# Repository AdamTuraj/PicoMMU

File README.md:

# PicoMMU

PicoMMU is a PCB designed to control a stepper motor and servo for a multi-material unit. It is compatible with Klipper firmware.

## Requirements

- A USB C cable to connect to your RPI / Printer
- A 12-24V power supply
- A TMC2209 (BTT Recommended)
- A stepper motor crimped with a 4 pin JST XH B4

## Flashing Klipper

1. Follow [this Klipper guide](https://www.klipper3d.org/Installation.html) on how to build the firmware. The first image shows the configuration settings and the second shows the "Optional Features" section.

2. Once the firmware is build, put the chip into DFU mode by clicking the reset button while holding the boot button.
3. Run lsusb and take not of the numbers in this format: xxxx:xxxx.
4. Now use the following command to flash the firmware (replacing xxxx:xxxx with your MCU's ID): `make flash FLASH_DEVICE=xxxx:xxxx`.
5. Unplug and replug in the USB cord and your MCU should pop up in `ls /dev/serial/by-id/*`.

## License

This project is licensed under the MIT License.

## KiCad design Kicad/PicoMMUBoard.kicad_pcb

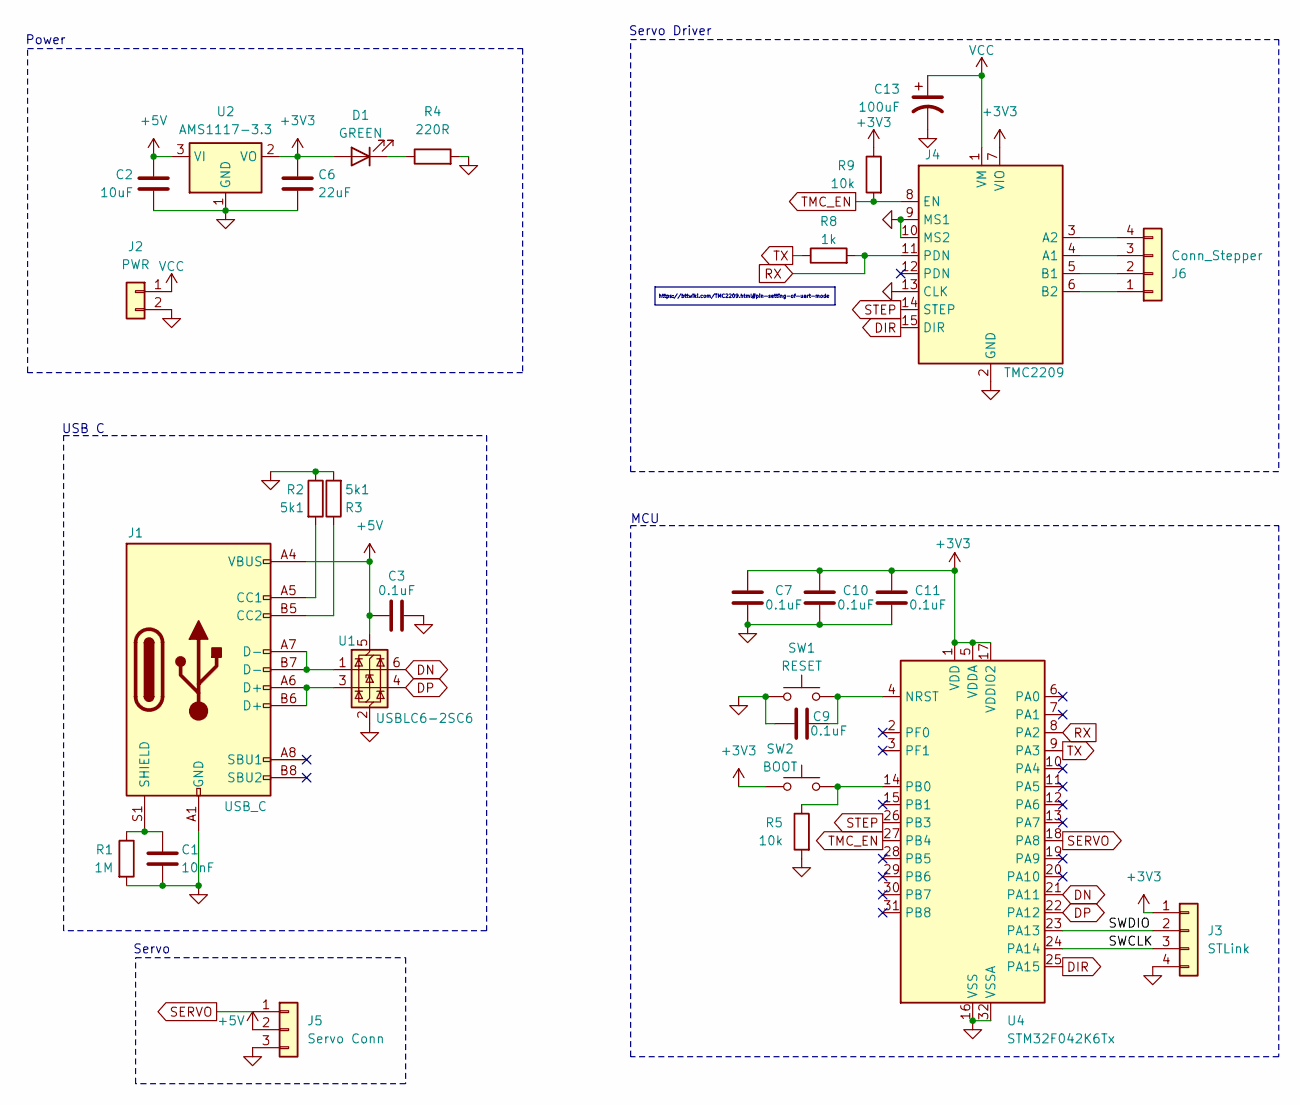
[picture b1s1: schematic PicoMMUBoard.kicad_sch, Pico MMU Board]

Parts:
C1: 10nF; C_0603_1608Metric
C2: 10uF; C_0603_1608Metric
C3, C7, C9, C10, C11: 0.1uF; C_0603_1608Metric
C6: 22uF; C_0603_1608Metric
C13: 100uF; C_Elec_6.3x7.7; LCSC C3151829
D1: GREEN; LED_0805_2012Metric; LCSC C2297
J1: USB_C; USB_C_Receptacle_GCT_USB4105-xx-A_16P_TopMnt_Horizontal; LCSC C165948
J2: PWR; TerminalBlock_MetzConnect_Type073_RT02602HBLU_1x02_P5.08mm_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; LCSC C8465
J3: STLink; PinHeader_1x04_P2.54mm_Vertical
J4: TMC2209
J5: Servo Conn; PinHeader_1x03_P2.54mm_Vertical; LCSC C144394
J6: Conn_Stepper; JST_XH_B4B-XH-A_1x04_P2.50mm_Vertical; LCSC C594232
R1: 1M; R_0603_1608Metric
R2, R3: 5k1; R_0603_1608Metric
R4: 220R; R_0603_1608Metric
R5, R9: 10k; R_0603_1608Metric
R8: 1k; R_0603_1608Metric
SW1: RESET; SW4_KMS-P; LCSC C221703
SW2: BOOT; SW4_KMS-P; LCSC C221703
U1: USBLC6-2SC6; SOT-23-6; LCSC C2827654
U2: AMS1117-3.3; SOT-223-3_TabPin2; LCSC C6186
U4: STM32F042K6Tx; LQFP-32_7x7mm_P0.8mm; LCSC C1337340

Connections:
+3V3: C6.1, C7.2, C10.2, C11.2, D1.2 (A), J3.1, J4.7 (VIO), R9.1, SW2.1, U2.2 (VO), U4.1 (VDD), U4.5 (VDDA), U4.17 (VDDIO2)
+5V: C2.1, C3.1, J1.A4 (VBUS), J1.A9 (VBUS), J1.B4 (VBUS), J1.B9 (VBUS), J5.2, U1.5 (VBUS), U2.3 (VI)
/SWCLK: J3.3, U4.24 (PA14)
/SWDIO: J3.2, U4.23 (PA13)
DIR: J4.15 (DIR), U4.25 (PA15)
DN: U1.6 (I/O1), U4.21 (PA11)
DP: U1.4 (I/O2), U4.22 (PA12)
GND: C1.2, C2.2, C3.2, C6.2, C7.1, C9.2, C10.1, C11.1, C13.2, J1.A1 (GND), J1.A12 (GND), J1.B1 (GND), J1.B12 (GND), J2.2, J3.4, J4.2 (GND), J4.9 (MS1), J4.10 (MS2), J4.13 (CLK), J5.3, R1.2, R2.1, R3.2, R4.2, R5.2, SW1.1, U1.2 (GND), U2.1 (GND), U4.16 (VSS), U4.32 (VSSA)
unnamed: D1.1 (K), R4.1
unnamed: J1.A5 (CC1), R2.2
unnamed: J1.B5 (CC2), R3.1
unnamed: J1.A6 (D+), J1.B6 (D+), U1.3 (I/O2)
unnamed: J1.A7 (D-), J1.B7 (D-), U1.1 (I/O1)
unnamed: C1.1, J1.S1 (SHIELD), R1.1
unnamed: J4.4 (A1), J6.3
unnamed: J4.3 (A2), J6.4
unnamed: J4.5 (B1), J6.2
unnamed: J4.6 (B2), J6.1
unnamed: C9.1, SW1.2, U4.4 (NRST)
unnamed: R5.1, SW2.2, U4.14 (PB0)
RX: J4.11 (PDN), R8.2, U4.8 (PA2)
SERVO: J5.1, U4.18 (PA8)
STEP: J4.14 (STEP), U4.26 (PB3)
TMC_EN: J4.8 (EN), R9.2, U4.27 (PB4)
TX: R8.1, U4.9 (PA3)
VCC: C13.1, J2.1, J4.1 (VM)

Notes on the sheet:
https://bttwiki.com/TMC2209.html#pin-setting-of-uart-mode
Power
Servo
MCU
USB C
Servo Driver

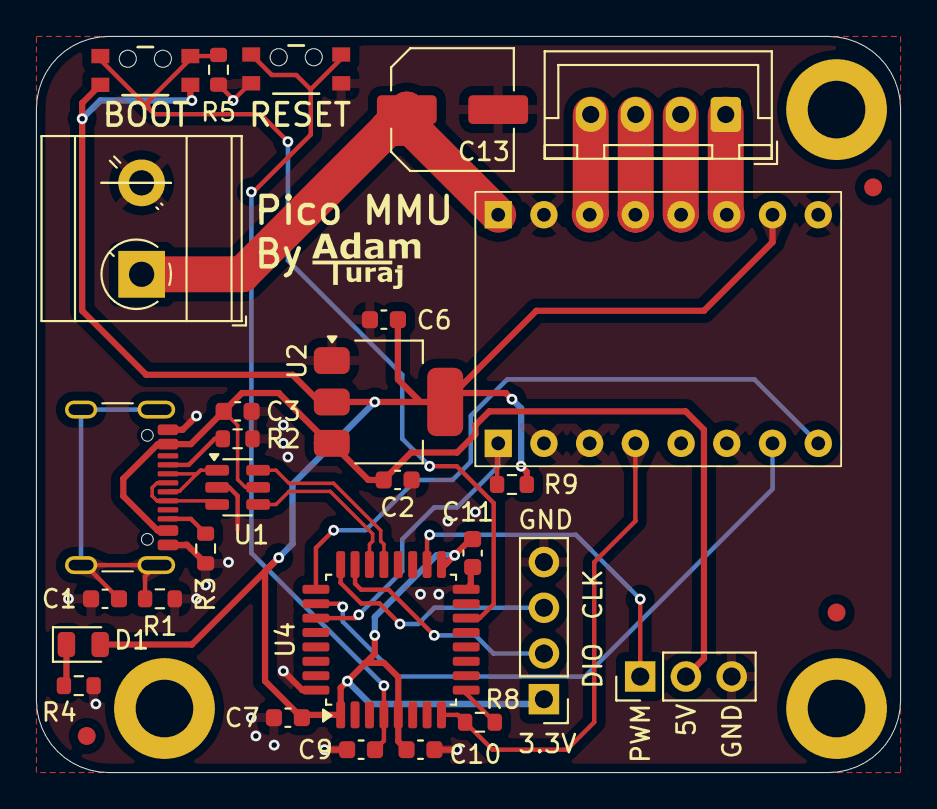
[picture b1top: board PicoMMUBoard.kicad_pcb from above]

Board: 2 copper layers, 48.0 x 40.9 mm, 28 parts (0 on the bottom side), 26 nets.

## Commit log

2025-01-24 Add v1.1
2025-01-24 Add image links and add optional features section image
2025-01-24 Clarify flashing guide
